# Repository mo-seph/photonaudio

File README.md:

# Quad LED Driver: audio over light

A four-channel analog LED driver for sending audio-rate signals through the air as light: soundcard → LED → air → phototransistor pickup → soundcard. Each channel is a linear voltage-controlled current sink (op-amp, transistor, sense resistor), so the light follows the signal rather than the LED's exponential V/I curve. Audio rides on an idle brightness set per channel by an on-board DAC or a trimmer. The design clips cleanly at off and at full when the input is overdriven, and the op-amp's supply rail sets a hard ceiling on LED current.

*Quad LED Driver Board v1.0 (November 2026): 170 × 100 mm, two layers. On the left is the 12 V input, the 5 V and 3.3 V supplies, and a XIAO ESP32-S3 with an MCP4728 four-channel DAC for the idle brightness. On the right are four identical channels A–D, each with a balanced audio input, DC lift, bias select (DAC or trimmer), amplifier, current sink and LED output.*

*The routing: top copper in red, bottom copper in blue, with the silkscreen. Each channel's current-sense return runs back separately to the star point at the main capacitor (the four diagonal tracks at bottom centre).*

## Status

- **v1.0 boards** arrived on 2026-11-17. Channel A, the supplies and the DAC are built and working, and channels B–D are next.
- **Channel A, measured** over a bench optical link (`measure/`): about 67 dB SNR unweighted (69 dB(A)) at 1% THD, with a −3 dB bandwidth of about 67 Hz to 20 kHz. The limit is the photosensor's distortion, not the driver.

## What's here

| Path | Contents |
|---|---|
| [OVERVIEW.md](OVERVIEW.md) | Goals and approach |
| [TUTORIAL.md](TUTORIAL.md) | How one channel works, part by part, with figures in `tutorial/` |
| [WORKING.md](WORKING.md) | Design notes, schematic and board reviews, measurement and bring-up log |
| [BRINGUP.md](BRINGUP.md) | Breadboard bring-up of one channel, power, XIAO and DAC |
| [build_plan/](build_plan/) | Staged build-and-test guide for the PCB (`index.html`, generated by `make_page.py`) |
| [BOM_pcb.md](BOM_pcb.md), [BOM_breadboard.md](BOM_breadboard.md) | Parts lists |
| [schematics/](schematics/) | Fusion Electronics (Eagle format) schematics and boards, PDF prints, and circuit drawings (`channel.png`, `dac.png`, `power.png`, `supply_filter.png`) |
| [cam_output/](cam_output/) | Gerbers as sent to JLCPCB for v1.0 |
| [fab/jlcpcb/](fab/jlcpcb/) | JLCPCB's CAM job and design rules for Fusion |
| [kicad/](kicad/) | The board converted to KiCad 10, checked against the Fusion original |
| [dac_test/](dac_test/) | Test firmware (PlatformIO) for the MCP4728 bias DAC |
| [measure/](measure/) | `linkmeasure`: frequency response, noise and distortion of the optical link, with every run's results |

In normal use, the board joins an I2C network of ESP32 devices as a Peripheral, with the four LED channels as one Element. That firmware lives in a separate repository.

Raw audio recordings from the measurements are not in the repository; each run keeps its analysed results (CSV, PNG, JSON).

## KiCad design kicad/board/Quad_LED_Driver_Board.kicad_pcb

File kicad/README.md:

# KiCad version of the board

`board/Quad_LED_Driver_Board.kicad_pcb` is `../schematics/Quad LED Driver Board.brd` (the v1.0 board, Fusion export of 2026-11-07 13:36) converted with KiCad 10.0.8's own Eagle importer. There is no KiCad schematic yet: see the end of this file.

## How it was checked (2026-11-24)

| Check | Result |
|---|---|
| Parts | All 182 Fusion parts, plus the 4 mounting holes as `UNK_HOLE_0`…`3` footprints |
| Nets | All 99 nets connect exactly the same pads as in Fusion |
| Copper | 864 top tracks, 140 bottom tracks, 123 vias, 12 pours: the same counts as Fusion |
| Connectivity | 0 unconnected after refilling the pours |
| DRC, with the board's own Fusion rules | 0 errors. 222 warnings, all silkscreen (labels overlapping each other, on pads, or near the edge), which Fusion doesn't check |

**Designators:** KiCad wants every designator to end in a digit, so the importer added a `0` to the 23 that don't: `R24B` → `R24B0`, `T_SC` → `T_SC0`, `PWR_IN` → `PWR_IN0`, `R13B` → `R13B0`, and so on. Those are the only renames.

**Design rules:** the import doesn't carry Fusion's design rules, so `tools/finish_board.py` copies them from the `.brd` (JLCPCB 2-layer: 0.127 mm clearance and track, 0.3 mm drill, 0.9 mm copper to edge, 0.1 mm solder-mask expansion) into the `.kicad_pro`. It also fills the pours.

## Re-running

From this folder, after a new export from Fusion:

```bash
export KICAD_DOCUMENTS_HOME="$PWD/kicad-user"
K=/Applications/KiCad/KiCad.app/Contents/MacOS/kicad-cli
KPY=/Applications/KiCad/KiCad.app/Contents/Frameworks/Python.framework/Versions/3.9/Resources/Python.app/Contents/MacOS/Python
BRD="../schematics/Quad LED Driver Board.brd"
PCB=board/Quad_LED_Driver_Board.kicad_pcb
$K pcb import --format eagle -o $PCB "$BRD"
$KPY tools/finish_board.py "$BRD" $PCB
$KPY tools/check_board_import.py "$BRD" $PCB
$K pcb drc --severity-all -o drc.rpt $PCB
$KPY tools/make_images.py "$BRD" $PCB ../images
```

`KICAD_DOCUMENTS_HOME` stops KiCad from scanning `~/Documents/KiCad` at start-up, which hangs on this Mac. `make_images.py` redraws the two README pictures from a copy of the board with the Fusion designators restored.

## Schematic

KiCad's command line can't import Eagle schematics; only the KiCad window can.

- **The Fusion export:** the cleanest result is a linked schematic and board. For that, export the quad board's own schematic from Fusion as `Quad LED Driver Board.sch`. Then use KiCad's **File → Import Non-KiCad Project → Eagle**, which pairs the `.sch` with the `.brd` of the same name.
- **`check_sch_import.py`:** compares an imported schematic's netlist with the Eagle `.sch`, net by net.
- **Do not use the KiCad MCP server's own Eagle translator.** It was tried on `Driver Channel.sch`: it made every ground symbol a separate part on its own net, so GND and K_GND fell apart.

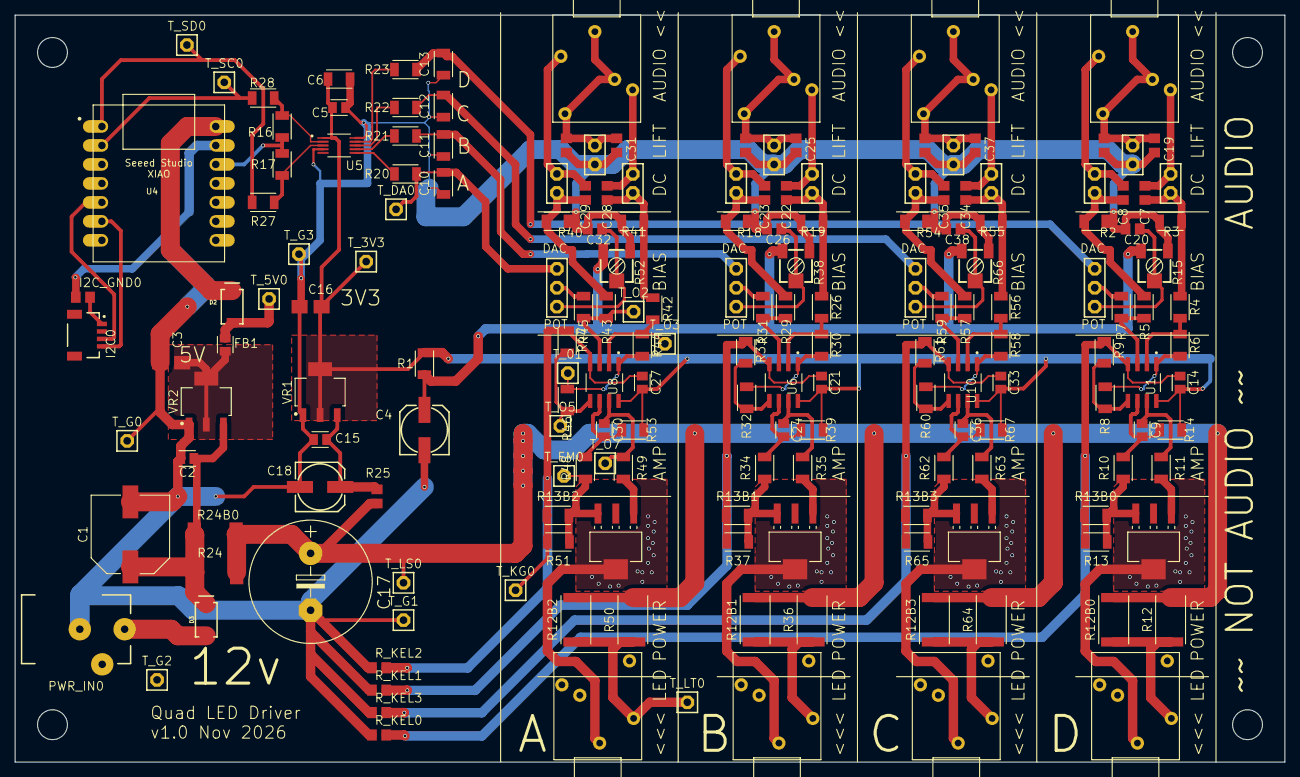
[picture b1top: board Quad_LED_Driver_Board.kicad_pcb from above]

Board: 2 copper layers, 170.0 x 100.0 mm, 186 parts (0 on the bottom side), 98 nets.

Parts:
AUDIO_IN0, AUDIO_IN1, AUDIO_IN2, AUDIO_IN3: 1503_091503_09_LMB; 1503_09_LMB
BIAS_SEL0, BIAS_SEL1, BIAS_SEL2, BIAS_SEL3: PINHD-1X3; 1X03
C1: 470uF; CAPAE1030X1050N
C2: 330nF; CAPC2012X110
C3, C16: 10uF; A_3216-18W
C4, C18: 100uF; 153CLV-0605
C5, C14, C15, C21, C27, C33: 100nF; CAPC2012X110
C6, C10, C11, C12, C13: 10uF; CAPC3216X135
C7, C8, C22, C23, C28, C29, C34, C35: 1uF; C0805
C9, C24, C30, C36: 1nF; CAPC2012X110
C17: 2200uF; E7,5-16
C19, C25, C31, C37: 10nF DNF; C0805
C20, C26, C32, C38: 10uF; C0805
D2: 1A/40V/500mV; SMA-DIODE
D3: 3A/40V/500mV; SMA-DIODE
FB1: 600R @ 100MHz; BEADC2012X105N
I2C0: QWIIC_RIGHT_ANGLE; JST04_1MM_RA
I2C_GND0: 0; R0805
J_DC_COLD0, J_DC_COLD1, J_DC_COLD2, J_DC_COLD3: PINHD-1X2; 1X02
J_DC_HOT0, J_DC_HOT1, J_DC_HOT2, J_DC_HOT3: PINHD-1X2; 1X02
J_LED0, J_LED1, J_LED2, J_LED3: 1503_091503_09_LMB; 1503_09_LMB
J_LIFT0, J_LIFT1, J_LIFT2, J_LIFT3: PINHD-1X2; 1X02
PWR_IN0: PJ-102AH
R1: 100R; RESC3216X70
R2, R3, R18, R19, R40, R41, R54, R55: 1M; RESC3216X70
R4, R5, R6, R7, R26, R29, R30, R31, R42, R43, R44, R45, R56, R57, R58, R59: 100k; RESC3216X70
R8, R16, R17, R32, R46, R60: 10k; RESC3216X70
R9, R33, R47, R61: 1.6k; RESC3216X70
R10, R20, R21, R22, R23, R34, R48, R62: 1k; RESC3216X70
R11, R35, R49, R63: 220R; RESC3216X70
R12, R36, R50, R64: 47R; RESC6332X71
R12B0, R12B1, R12B2, R12B3: 47R HPO; RESC6332X71
R13, R37, R51, R65: 4.7R; RESC3216X70
R13B0, R13B1, R13B2, R13B3: 4.7R HPO; RESC3216X70
R14, R39, R53, R67: 470k; RESC3216X70
R15, R38, R52, R66: 10k; RTRIM3314J
R24, R24B0: 2.2; R2512
R25: 22; R0805
R27, R28: 220; RESC3216X70
R_KEL0, R_KEL1, R_KEL2, R_KEL3: 0; R0805
R_LIFT0, R_LIFT1, R_LIFT2, R_LIFT3: 0; R0805
T_01, T_3V3, T_5V0: PINHD-1X1; 1X01
T_DA0: PINHD-1X1; 1X01
T_EM0: PINHD-1X1; 1X01
T_G0, T_G1, T_G2, T_G3: PINHD-1X1; 1X01
T_KG0: PINHD-1X1; 1X01
T_LS0: PINHD-1X1; 1X01
T_LT0: PINHD-1X1; 1X01
T_O2, T_O3, T_O5, T_O7: PINHD-1X1; 1X01
T_SC0: PINHD-1X1; 1X01
T_SD0: PINHD-1X1; 1X01
U1, U6, U8, U10: MCP6002-I/SN; SOIC127P600X175-8N
U2, U3, U7, U9: BCP56-16; SOT-223_3P7X6P7_ONS
U4: XIAO-THRUHOLEHYBRID-SMT-THT; XIAO-GENERIC-HYBRID-MODULE14P-2.54-21X17.8MM
U5: MCP4728-E/UN; SOP50P490X110-10N
UNK_HOLE_0: dummyfp0
UNK_HOLE_1: dummyfp1
UNK_HOLE_2: dummyfp2
UNK_HOLE_3: dummyfp3
VR1: LD1117_3v3; SOT230P700X170-4
VR2: LD1117_5V; SOT230P700X170-4

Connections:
3V3_A: C5.1, C6.1, C14.2, C16.+, C21.2, C27.2, C33.2, R1.2, R14.2, R39.2, R53.2, R67.2, T_3V3.1, U1.8, U5.1, U6.8, U8.8, U10.8, VR1.2, VR1.4
3V3_BIAS: C4.+, R1.1, R15.1, R38.1, R52.1, R66.1
5V_RAW: C3.+, FB1.1, VR2.2, VR2.4
5V_XIAO: D2.A, FB1.2, T_5V0.1
12V_RAW: C1.1, C2.1, D3.C, R24.1, R24B0.1, VR2.3
+3V3_XIAO: R16.1, R17.2, U4.12
+12: D3.A, PWR_IN0.1
DAC_A: BIAS_SEL2.1, C10.2, R20.1, T_DA0.1
DAC_B: BIAS_SEL1.1, C11.2, R21.1
DAC_C: BIAS_SEL3.1, C12.2, R22.1
DAC_D: BIAS_SEL0.1, C13.2, R23.1
GND: C1.2, C2.2, C3.-, C4.-, C5.2, C6.2, C10.1, C11.1, C12.1, C13.1, C15.2, C16.-, C17.-, C18.-, C19.2, C20.2, C25.2, C26.2, C31.2, C32.2, C37.2, C38.2, I2C_GND0.1, J_LIFT0.2, J_LIFT1.2, J_LIFT2.2, J_LIFT3.2, PWR_IN0.2, R2.1, R3.2, R15.3, R18.1, R19.2, R38.3, R40.1, R41.2, R52.3, R54.1, R55.2, R66.3, R_KEL0.1, R_KEL1.1, R_KEL2.1, R_KEL3.1, R_LIFT0.1, R_LIFT1.1, R_LIFT2.1, R_LIFT3.1, T_G0.1, T_G1.1, T_G2.1, T_G3.1, U4.13, U5.4, U5.10, VR1.1, VR2.1
K_GND_A: C27.1, R13B2.1, R47.1, R51.1, R_KEL2.2, T_KG0.1, U8.4
K_GND_B: C21.1, R13B1.1, R33.1, R37.1, R_KEL1.2, U6.4
K_GND_C: C33.1, R13B3.1, R61.1, R65.1, R_KEL3.2, U10.4
K_GND_D: C14.1, R9.1, R13.1, R13B0.1, R_KEL0.2, U1.4
LED_SUPPLY: C17.+, R12.2, R12B0.2, R12B1.2, R12B2.2, R12B3.2, R24.2, R24B0.2, R25.1, R36.2, R50.2, R64.2, T_LS0.1
unnamed: D2.C, U4.14
unnamed: I2C0.1, I2C_GND0.2
unnamed: C15.1, C18.+, R25.2, VR1.3
unnamed: C8.1, J_DC_COLD0.1, R2.2, R5.1
unnamed: C7.1, J_DC_HOT0.2, R3.1, R4.1
unnamed: R4.2, R6.1, U1.2
unnamed: R5.2, R7.1, U1.3
unnamed: R6.2, R8.1, U1.1
unnamed: R8.2, R9.2, U1.5
unnamed: R11.2, U3.1
unnamed: J_LED0.2, R12.1, R12B0.1
unnamed: R10.2, R13.2, R13B0.2, U3.3
unnamed: C9.1, R11.1, U1.7
unnamed: C9.2, R10.1, R14.1, U1.6
unnamed: AUDIO_IN0.2, C8.2, J_DC_COLD0.2
unnamed: BIAS_SEL0.2, R7.2
unnamed: AUDIO_IN0.3, C7.2, J_DC_HOT0.1
unnamed: BIAS_SEL0.3, C20.1, R15.2
unnamed: J_LED0.1, U3.4
unnamed: C23.1, J_DC_COLD1.1, R18.2, R29.1
unnamed: R16.2, R28.1, U5.2
unnamed: R17.1, R27.1, U5.3
unnamed: R20.2, U5.6
unnamed: R21.2, U5.7
unnamed: R22.2, U5.8
unnamed: R23.2, U5.9
unnamed: C22.1, J_DC_HOT1.2, R19.1, R26.1
unnamed: R26.2, R30.1, U6.2
unnamed: R29.2, R31.1, U6.3
unnamed: R30.2, R32.1, U6.1
unnamed: R32.2, R33.2, U6.5
unnamed: R35.2, U2.1
unnamed: J_LED1.2, R12B1.1, R36.1
unnamed: R13B1.2, R34.2, R37.2, U2.3
unnamed: C24.1, R35.1, U6.7
unnamed: C24.2, R34.1, R39.1, U6.6
unnamed: AUDIO_IN1.2, C23.2, J_DC_COLD1.2
unnamed: BIAS_SEL1.2, R31.2
unnamed: AUDIO_IN1.3, C22.2, J_DC_HOT1.1
unnamed: BIAS_SEL1.3, C26.1, R38.2
unnamed: J_LED1.1, U2.4
unnamed: C29.1, J_DC_COLD2.1, R40.2, R43.1
unnamed: C28.1, J_DC_HOT2.2, R41.1, R42.1
unnamed: R42.2, R44.1, T_O3.1, U8.2
unnamed: R43.2, R45.1, T_O2.1, U8.3
unnamed: R44.2, R46.1, T_01.1, U8.1
unnamed: R46.2, R47.2, T_O5.1, U8.5
unnamed: R49.2, U7.1
unnamed: J_LED2.2, R12B2.1, R50.1, T_LT0.1
unnamed: R13B2.2, R48.2, R51.2, T_EM0.1, U7.3
unnamed: C30.1, R49.1, T_O7.1, U8.7
unnamed: C30.2, R48.1, R53.1, U8.6
unnamed: AUDIO_IN2.2, C29.2, J_DC_COLD2.2
unnamed: BIAS_SEL2.2, R45.2
unnamed: AUDIO_IN2.3, C28.2, J_DC_HOT2.1
unnamed: BIAS_SEL2.3, C32.1, R52.2
unnamed: J_LED2.1, U7.4
unnamed: C35.1, J_DC_COLD3.1, R54.2, R57.1
unnamed: C34.1, J_DC_HOT3.2, R55.1, R56.1
unnamed: R56.2, R58.1, U10.2
unnamed: R57.2, R59.1, U10.3
unnamed: R58.2, R60.1, U10.1
unnamed: R60.2, R61.2, U10.5
unnamed: R63.2, U9.1
unnamed: J_LED3.2, R12B3.1, R64.1
unnamed: R13B3.2, R62.2, R65.2, U9.3
unnamed: C36.1, R63.1, U10.7
unnamed: C36.2, R62.1, R67.1, U10.6
unnamed: AUDIO_IN3.2, C35.2, J_DC_COLD3.2
unnamed: BIAS_SEL3.2, R59.2
unnamed: AUDIO_IN3.3, C34.2, J_DC_HOT3.1
unnamed: BIAS_SEL3.3, C38.1, R66.2
unnamed: J_LED3.1, U9.4
SCL_DAC: R28.2, T_SC0.1, U4.2
SCL_NET: I2C0.4, U4.6
SDA_DAC: R27.2, T_SD0.1, U4.1
SDA_NET: I2C0.3, U4.5
SLEEVE_A: AUDIO_IN2.1, AUDIO_IN2.4, AUDIO_IN2.5, C31.1, J_LIFT2.1, R_LIFT2.2
SLEEVE_B: AUDIO_IN1.1, AUDIO_IN1.4, AUDIO_IN1.5, C25.1, J_LIFT1.1, R_LIFT1.2
SLEEVE_C: AUDIO_IN3.1, AUDIO_IN3.4, AUDIO_IN3.5, C37.1, J_LIFT3.1, R_LIFT3.2
SLEEVE_D: AUDIO_IN0.1, AUDIO_IN0.4, AUDIO_IN0.5, C19.1, J_LIFT0.1, R_LIFT0.2

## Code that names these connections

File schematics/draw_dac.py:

"""DAC section, 3.3 V analog version (2026-10-23): XIAO + MCP4728 + output smoothing.
The DAC runs from +3V3_A, so it talks to the XIAO directly - no level shifter (Q2, Q3, R18, R19 removed;
R16/R17 stay as the 4.7k bus pull-ups).
Designators follow 'LED Driver.sch'. BIAS_SEL pin 1 <- DAC_x is the intended wiring.
Power rails are shown as net labels (open dots) rather than drawn wires.
v1 (2026-11-04, from the DAC update-noise tests; new / changed parts in orange):
  C10-C13 1 µF -> 10 µF (16 Hz: zipper noise from ramps −13 dB, measured);
  R16/R17 4.7k to +3V3_A -> 10k to the XIAO's 3V3 (pull-up current off the analog rail);
  R27/R28 220 Ω in series at the XIAO's SDA/SCL pins.
Run: python draw_dac.py -> dac.svg / dac.png"""
import schemdraw
import schemdraw.elements as elm
from schemdraw.elements import IcPin

PIN = 1.5  # pin spacing, so the bus rows line up with the DAC pins
NEW = '#c2410c'   # new / changed for v1

with schemdraw.Drawing(show=False) as d:
    d.config(bgcolor='#fcfcfb', margin=0.6, fontsize=11, unit=2.0)

    # ---- U4: XIAO ESP32-S3 -------------------------------------------------------------
    xiao = elm.Ic(pins=[
        IcPin(name='5V', side='top', slot='1/2'),
        IcPin(name='3V3', side='top', slot='2/2', anchorname='V33'),
        IcPin(name='GND', side='bottom'),
        IcPin(name='D4 (GPIO5)', side='left', slot='2/2', anchorname='D4'),
        IcPin(name='D5 (GPIO6)', side='left', slot='1/2', anchorname='D5'),
        IcPin(name='D0 (GPIO1)', side='right', slot='2/2', anchorname='D0'),
        IcPin(name='D1 (GPIO2)', side='right', slot='1/2', anchorname='D1'),
    ], size=(5.5, 3.5), pinspacing=PIN, leadlen=0.6)

    elm.Line().at(xiao['5V']).up(1.0)
    elm.Dot(open=True).label('XIAO_5V', 'left')
    elm.Line().at(xiao.V33).up(1.0).color(NEW)
    elm.Dot(open=True).label('XIAO_3V3 (output)', 'right').color(NEW)
    elm.Line().at(xiao.GND).down(0.5)
    elm.Ground()
    elm.Label().at((xiao.GND[0] + 0.4, xiao.GND[1] - 0.3)).label('U4  XIAO ESP32-S3', fontsize=11, halign='left')

    # Network I2C to the Central (Wire, slave) on connector J2
    elm.Line().at(xiao.D4).left(2.0)
    elm.Dot(open=True).label('J2 SDA_NET', 'left')
    elm.Line().at(xiao.D5).left(2.0)
    elm.Dot(open=True).label('J2 SCL_NET', 'left')
    elm.Dot(open=True).at((xiao.D5[0] - 2.0, xiao.D5[1] - 1.5)).label('J2 GND', 'left')
    elm.Ground()

    # ---- DAC bus (Wire1), 3.3 V on both sides: 220 Ω series at the XIAO, 10k pull-ups to the XIAO's 3V3 ----
    elm.Resistor().at(xiao.D0).right().label('R27 220Ω', loc='top', fontsize=10).color(NEW)
    elm.Line().right(0.5)
    sda = elm.Dot()
    elm.Resistor().at(sda.center).up().label('R17 10k', loc='bottom', fontsize=10).color(NEW)
    elm.Dot(open=True).label('XIAO_3V3', 'top', fontsize=10).color(NEW)
    elm.Line().at(sda.center).right(4.5)
    elm.Label().at((sda.center[0] + 1.0, sda.center[1] + 0.3)).label('SDA_DAC', fontsize=9, halign='left')
    sda_end = d.here

    elm.Resistor().at(xiao.D1).right().label('R28 220Ω', loc='bottom', fontsize=10).color(NEW)
    elm.Line().right(2.0)
    scl = elm.Dot()
    elm.Resistor().at(scl.center).down().label('R16 10k', loc='top', fontsize=10).color(NEW)
    elm.Dot(open=True).label('XIAO_3V3', 'bottom', fontsize=10).color(NEW)
    elm.Line().at(scl.center).right(3.0)
    elm.Label().at((scl.center[0] + 0.5, scl.center[1] + 0.3)).label('SCL_DAC', fontsize=9, halign='left')

    # ---- U5: MCP4728 ---------------------------------------------------------------------
    dac = elm.Ic(pins=[
        IcPin(name='VDD', pin='1', side='top'),
        IcPin(name='SDA', pin='3', side='left', slot='4/4'),
        IcPin(name='SCL', pin='2', side='left', slot='3/4'),
        IcPin(name='~LDAC', pin='4', side='left', slot='2/4', anchorname='LDAC'),
        IcPin(name='RDY/~BSY', pin='5', side='left', slot='1/4', anchorname='RDY'),
        IcPin(name='VOUTA', pin='6', side='right', slot='4/4'),
        IcPin(name='VOUTB', pin='7', side='right', slot='3/4'),
        IcPin(name='VOUTC', pin='8', side='right', slot='2/4'),
        IcPin(name='VOUTD', pin='9', side='right', slot='1/4'),
        IcPin(name='VSS', pin='10', side='bottom'),
    ], size=(4.5, 6.5), pinspacing=PIN, leadlen=0.6).anchor('SDA').at(sda_end) \
        .label('U5\nMCP4728', 'center', fontsize=11)

    elm.Line().at(dac.LDAC).left(1.0)
    elm.Ground().label('tied low', 'bottom', fontsize=9)
    elm.Line().at(dac.RDY).left(1.0)
    elm.Label().label('NC', loc='left', fontsize=9)
    elm.Line().at(dac.VSS).down(0.5)
    elm.Ground()

    # VDD from the clean analog 3.3 V, decoupled right at the pin
    elm.Line().at(dac.VDD).up(3.5)
    vdd = elm.Dot()
    elm.Dot(open=True).at((vdd.center[0], vdd.center[1] + 0.6)).label('+3V3_A', 'top')
    elm.Line().at(vdd.center).up(0.6)
    elm.Line().at(vdd.center).right(1.5)
    elm.Dot()
    d.push(); elm.Capacitor().down().label('C5\n100nF', loc='bottom', fontsize=10); elm.Ground(); d.pop()
    elm.Line().right(1.5)
    elm.Capacitor().down().label('C6\n10µF', loc='bottom', fontsize=10)
    elm.Ground()

    # ---- Output smoothing, fanned out so the caps don't cross other outputs ------------------
    jogs = {'VOUTA': 3.0, 'VOUTB': 0.75, 'VOUTC': -0.75, 'VOUTD': -3.0}
    for i, (pin, ch) in enumerate([('VOUTA', 'A'), ('VOUTB', 'B'), ('VOUTC', 'C'), ('VOUTD', 'D')]):
        p = dac.absanchors[pin]
        elm.Line().at(p).right(0.5)
        elm.Line().toy(p[1] + jogs[pin])
        elm.Line().right(0.5)
        elm.Resistor().right().label(f'R{20 + i} 1k', fontsize=10)
        n = elm.Dot()
        elm.Line().right(2.0)
        elm.Dot(open=True).label(f'DAC_{ch} → channel {ch}, BIAS_SEL pin 1', 'right', fontsize=10)
        elm.Capacitor().at(n.center).down().label(f'C{10 + i} 10µF', loc='bottom', fontsize=10).color(NEW)
        elm.Ground()

    elm.Label().at((dac.VSS[0], dac.VSS[1] - 6.0)).label(
        'MCP4728 (MSOP-10): default I2C address 0x60, on the XIAO\'s second I2C bus (Wire1: D0 = SDA, D1 = SCL)\n'
        'Runs from +3V3_A, same as the XIAO\'s logic: no level shifter needed.  ~LDAC tied low\n'
        'Reference = VDD (set in firmware) → DAC_x = 0–3.3 V, same range as the trimmer and the U1A clamp → full current.\n'
        '    Internal 2.048 V reference also works: 0.5 mV steps (≈ −5 dB zipper); the bias then tops out at 62% of full scale\n'
        'Smoothing: 1k + 10µF ≈ 16 Hz (ramp zipper −13 dB). R kept at 1k so it barely upsets the difference amp\'s 100k balance\n'
        'Each DAC write adds a click (500 writes/s = a 500 Hz comb): firmware writes only when the value changes.\n'
        'Layout: SDA/SCL short, over unbroken ground, away from J1 / U1A / Vbias / R13; C5/C6 at U5\'s pins;\n'
        '    XIAO / U5 ground returns kept local. XIAO off USB in use (a USB loop adds hum; use a USB isolator for development)',
        fontsize=10)

    d.save('dac.svg', transparent=False)
    d.save('dac.png', transparent=False, dpi=150)
